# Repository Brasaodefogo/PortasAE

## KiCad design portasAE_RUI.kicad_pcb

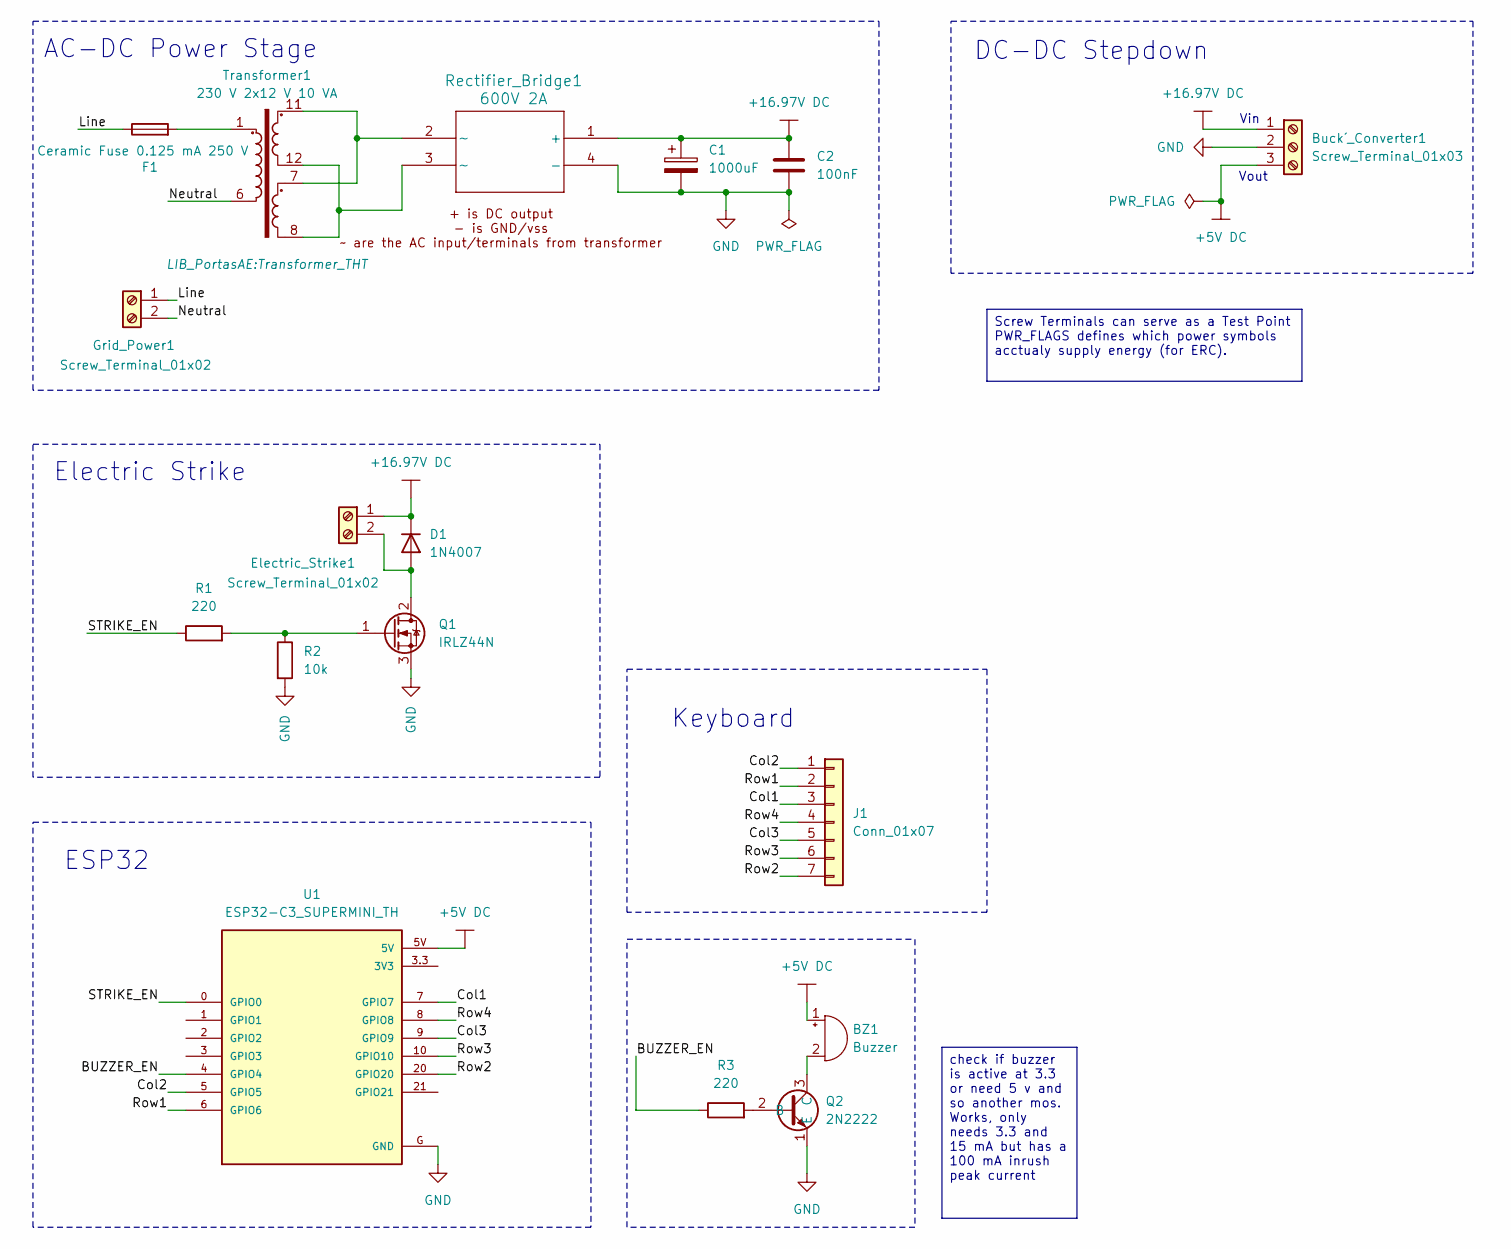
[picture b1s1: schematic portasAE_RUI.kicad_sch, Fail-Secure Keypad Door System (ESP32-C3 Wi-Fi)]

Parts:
BZ1: Buzzer; Buzzer_THT
Buck´_Converter1: Screw_Terminal_01x03; Screw_Terminal_01x03_THT
C1: 1000uF; CP_Radial_D10.0mm_P5.00mm
C2: 100nF; C_Disc_D3.0mm_W1.6mm_P2.50mm
D1: 1N4007; D_DO-41_SOD81_P10.16mm_Horizontal
Electric_Strike1: Screw_Terminal_01x02; Screw_Terminal_01x02_THT
F1: Ceramic Fuse 0.125 mA 250 V; Fuse_Holder_THT
Grid_Power1: Screw_Terminal_01x02; Screw_Terminal_01x02_THT
J1: Conn_01x07; PinHeader_1x07_P2.54mm_Vertical
Q1: IRLZ44N; TO-220-3_Vertical
Q2: 2N2222; TO-92_Inline_Wide
R1, R3: 220; R_axiaxl_THT_pitch_6,8mm_hole_0,46
R2: 10k; R_axiaxl_THT_pitch_6,8mm_hole_0,46
Rectifier_Bridge1: 600V 2A; Rectifier_Bridge
Transformer1: 230 V 2x12 V 10 VA; Transformer_THT
U1: ESP32-C3_SUPERMINI_TH; MODULE_ESP32-C3_SUPERMINI_TH

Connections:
+5V DC: BZ1.1 (+), Buck´_Converter1.3, U1.5V; also elsewhere on the board
+16.97V DC: Buck´_Converter1.1, C1.1, C2.1, D1.1 (K), Electric_Strike1.1, Rectifier_Bridge1.1 (+); also elsewhere on the board
/BUZZER_EN: R3.1, U1.4 (GPIO4)
/Col1: J1.3, U1.7 (GPIO7)
/Col2: J1.1, U1.5 (GPIO5)
/Col3: J1.5, U1.9 (GPIO9)
/Line: F1.1, Grid_Power1.1
/Neutral: Grid_Power1.2, Transformer1.6
/Row1: J1.2, U1.6 (GPIO6)
/Row2: J1.7, U1.20 (GPIO20)
/Row3: J1.6, U1.10 (GPIO10)
/Row4: J1.4, U1.8 (GPIO8)
/STRIKE_EN: R1.1, U1.0 (GPIO0)
GND: Buck´_Converter1.2, C1.2, C2.2, Q1.3 (S), Q2.1 (E), R2.2, Rectifier_Bridge1.4 (-), U1.G (GND); also elsewhere on the board
unnamed: BZ1.2 (-), Q2.3 (C)
unnamed: D1.2 (A), Electric_Strike1.2, Q1.2 (D)
unnamed: F1.2, Transformer1.1
unnamed: Q1.1 (G), R1.2, R2.1
unnamed: Q2.2 (B), R3.2
unnamed: Rectifier_Bridge1.2 (∼), Transformer1.7, Transformer1.11
unnamed: Rectifier_Bridge1.3 (∼), Transformer1.8, Transformer1.12

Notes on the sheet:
Vout
Electric Strike
ESP32
Vin
Keyboard
DC-DC Stepdown
AC-DC Power Stage
Screw Terminals can serve as a Test Point PWR_FLAGS defines which power symbols acctualy supply energy (for ERC).
check if buzzer is active at 3.3 or need 5 v and so another mos. Works, only needs 3.3 and 15 mA but has a 100 mA inrush peak current

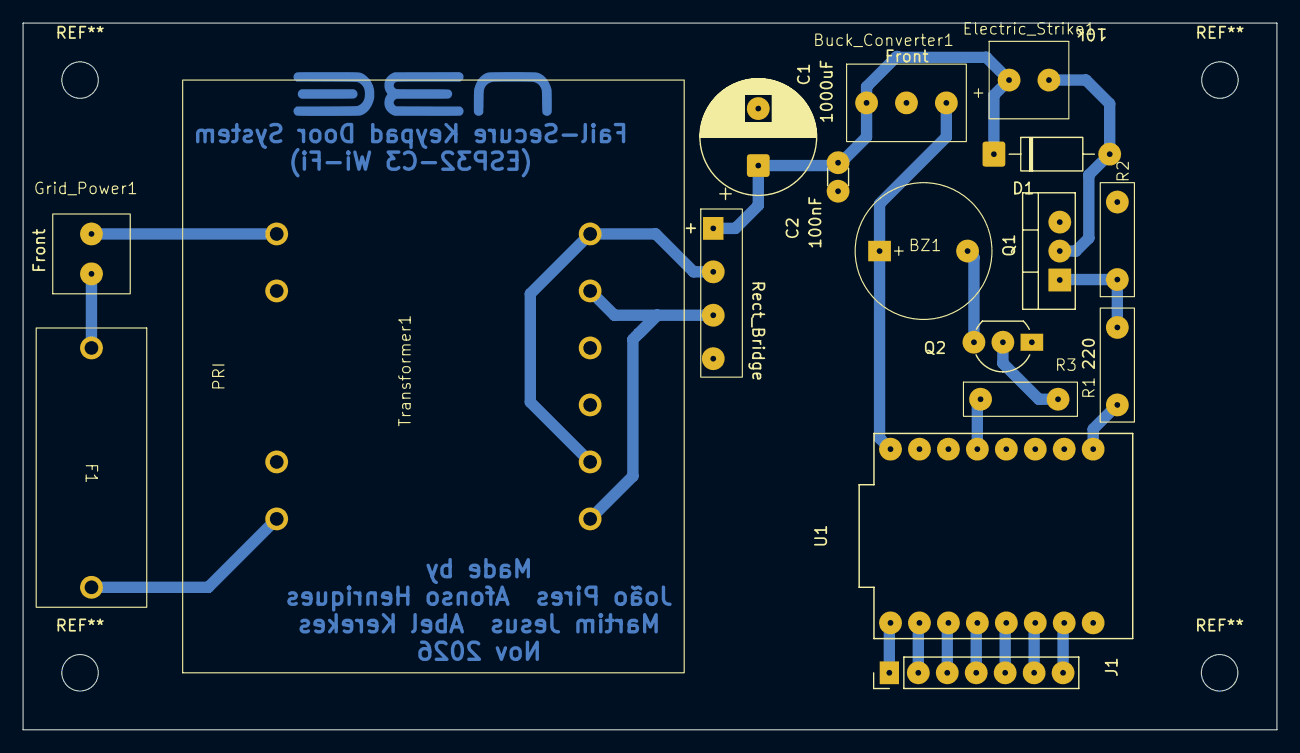
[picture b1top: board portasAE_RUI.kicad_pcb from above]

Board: 2 copper layers, 110.0 x 62.0 mm, 17 parts (0 on the bottom side), 21 nets.

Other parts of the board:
Buck_Converter1: Screw_Terminal_01x03; Screw_Terminal_01x03_THT

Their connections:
+5V DC: Buck_Converter1.3; also elsewhere on the board
+16.97V DC: Buck_Converter1.1; also elsewhere on the board
GND: Buck_Converter1.2; also elsewhere on the board
